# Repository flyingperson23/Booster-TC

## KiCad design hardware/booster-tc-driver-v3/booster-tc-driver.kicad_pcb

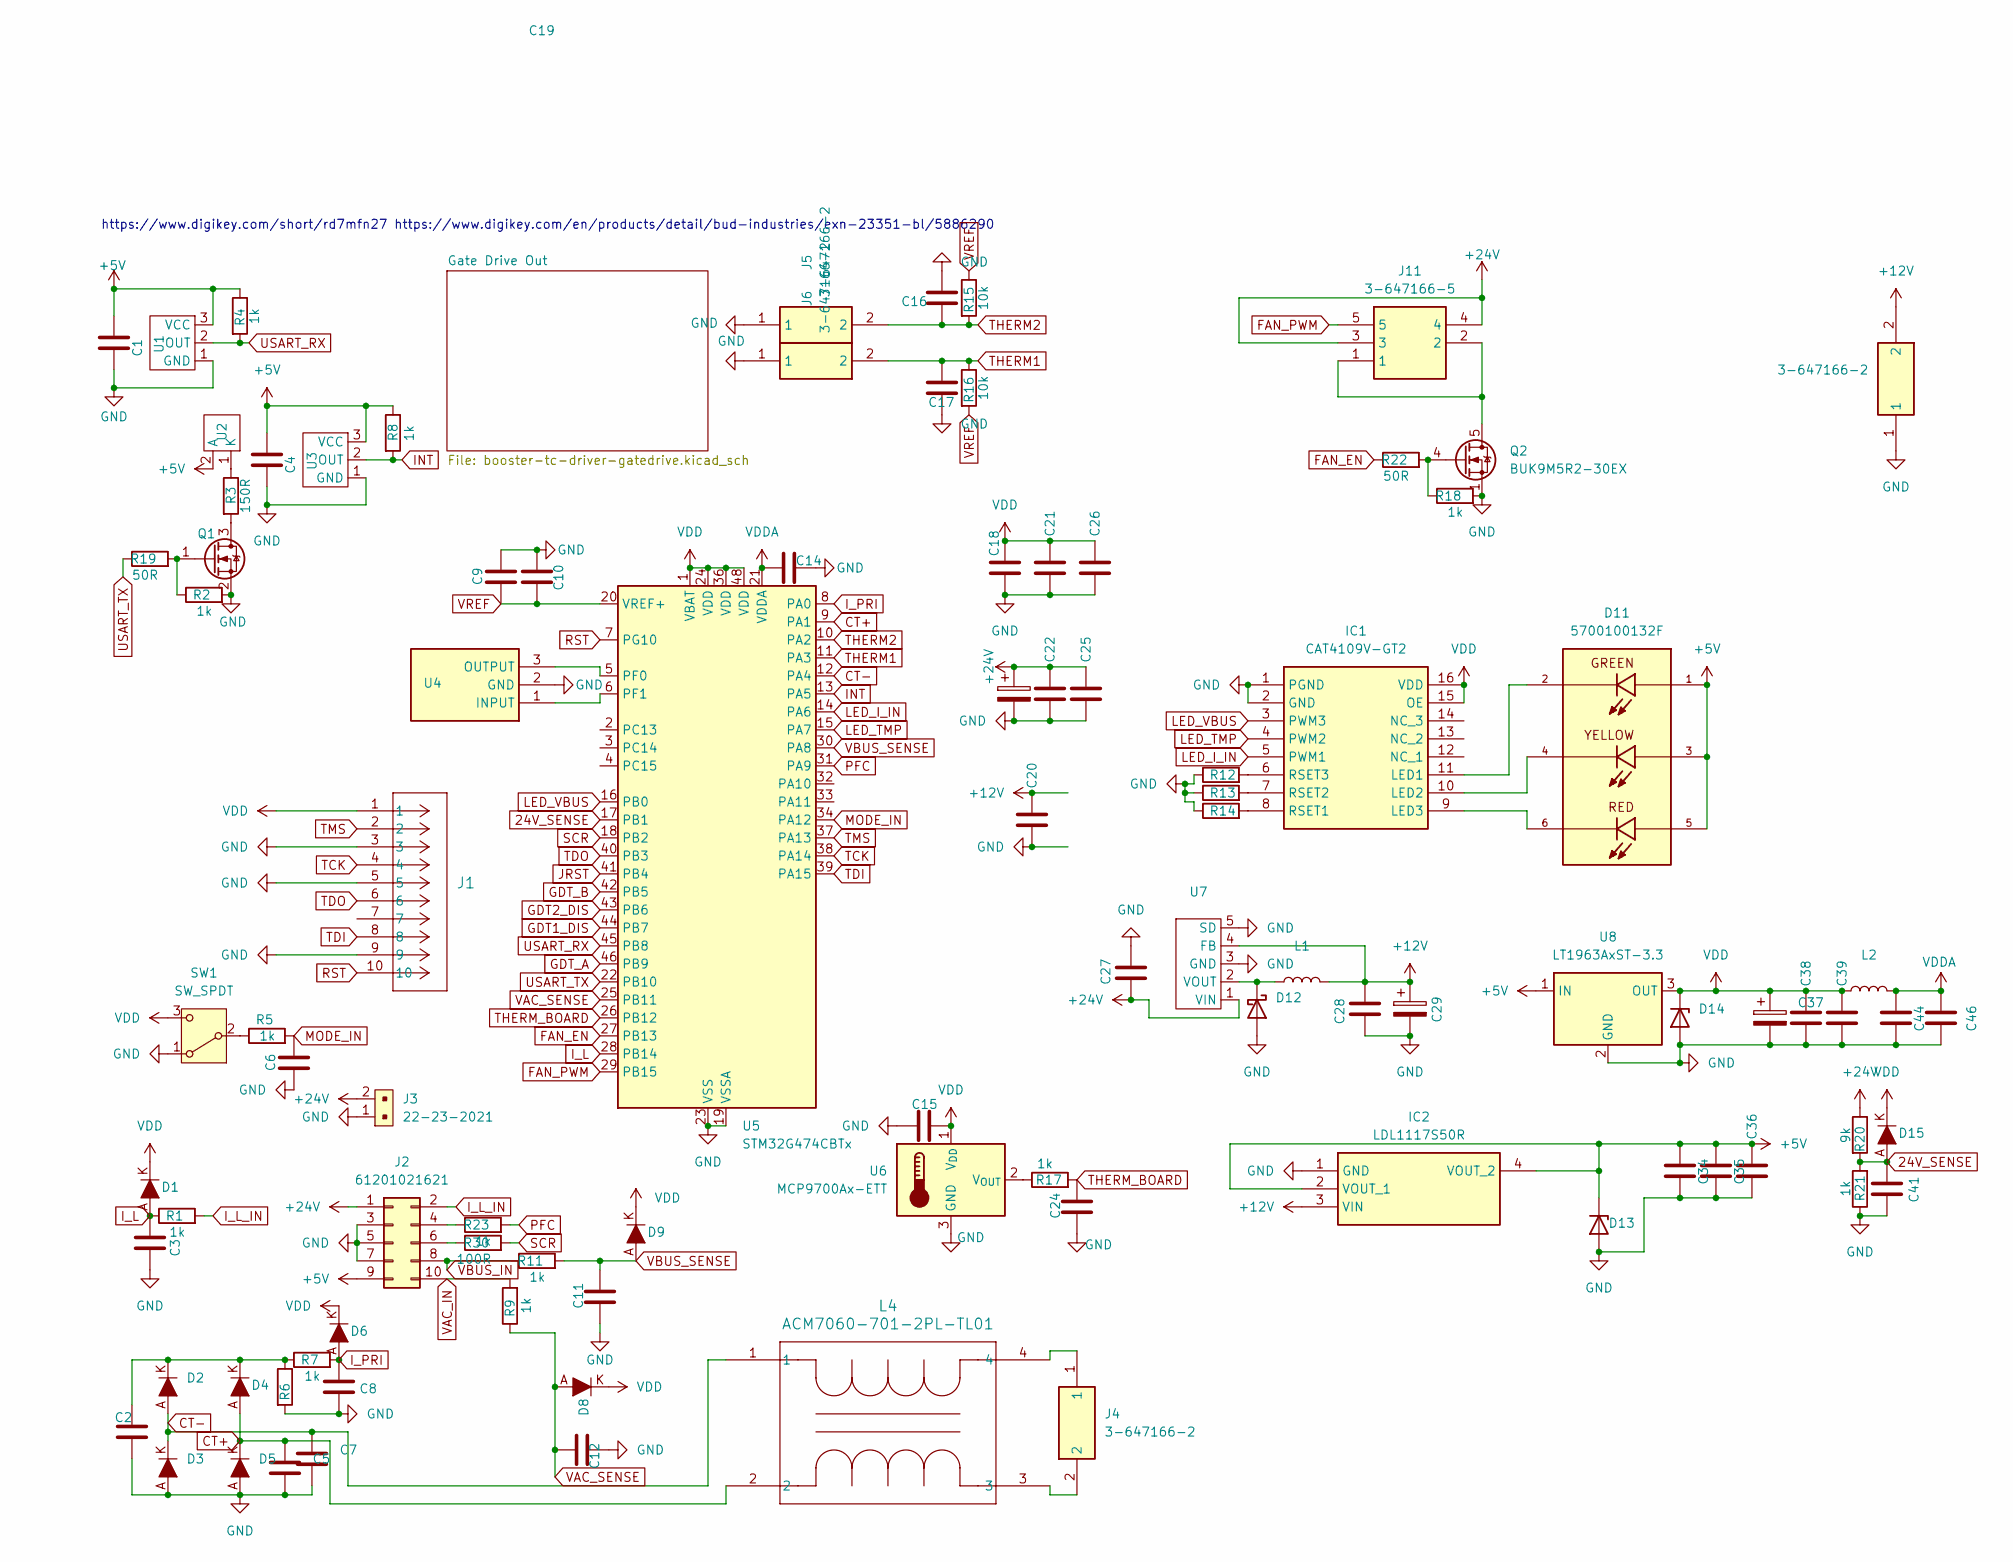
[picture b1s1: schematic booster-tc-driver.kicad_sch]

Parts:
C1, C4, C6, C9, C34, C35, C44: 2u2; C_0603_1608Metric_Pad1.08x0.95mm_HandSolder
C2, C3, C8: 1n; C_0603_1608Metric_Pad1.08x0.95mm_HandSolder
C5, C7: 150p; C_0603_1608Metric_Pad1.08x0.95mm_HandSolder
C10, C14, C15, C16, C17, C18, C20, C21, C22, C25, C26, C27, C28, C36, C38, C39, C41, C46: .1uf; C_0603_1608Metric_Pad1.08x0.95mm_HandSolder
C11, C12, C24: 10n; C_0603_1608Metric_Pad1.08x0.95mm_HandSolder
C19: 330u 860020575013; 860020575013
C29, C37: 470u 860020474014; CAPPRD350W52D800H1300
D1, D2, D3, D4, D5, D6, D8, D9, D15: 1N5819HW-7-F; SOD-123; MPN 1N5819HW-7-F
D11: 5700100132F; LED_5700100132F; PARTREV N
D12: PMEG4050EP; D_SOD-128
D13: SMBJ5.0A-TR; DO-214AA
D14: SMBJ3V3; DO-214AA
IC1: CAT4109V-GT2; Mouser Part Number 698-CAT4109V-GT2
IC2: LDL1117S50R; SOT230P700X180-4N; Mouser Part Number 511-LDL1117S50R
J1: 62201021121; CONN_62201021121_WRE
J2: 61201021621; IDC-Header_2x05_P2.54mm_Vertical
J3: 22-23-2021; PinHeader_1x2_P2.54mm_Drill1.02mm; MPN 22-23-2021
J4, J5, J6, J7: 3-647166-2; 36471662; Mouser Part Number 571-3-647166-2
J11: 3-647166-5; 36471665; Mouser Part Number 571-3-647166-5
L1: 22u IHLP3232DZER220M5A; IND_IHLP-3232DZ_VIS-M
L2: 4u7 LQM2MPN4R7NG0L; LQM2MPN4R7NG0L
L4: ACM7060-701-2PL-TL01; IND_ACM7060_TDK
Q1: T2N7002AK; SOT-23
Q2: BUK9M5R2-30EX; LFPAK33
R1, R2, R4, R5, R7, R8, R9, R11, R17, R18, R21, R23: 1k; R_0603_1608Metric_Pad0.98x0.95mm_HandSolder
R3: 150R; R_0603_1608Metric_Pad0.98x0.95mm_HandSolder
R6: 2R2 35222R2JT; R_2512_6332Metric_Pad1.40x3.35mm_HandSolder
R12, R13, R14: 24k9; R_0603_1608Metric_Pad0.98x0.95mm_HandSolder
R15, R16: 10k; R_0603_1608Metric_Pad0.98x0.95mm_HandSolder
R19, R22: 50R; R_0603_1608Metric_Pad0.98x0.95mm_HandSolder
R20: 9k; R_0603_1608Metric_Pad0.98x0.95mm_HandSolder
R30: 100R; R_0603_1608Metric_Pad0.98x0.95mm_HandSolder
SW1: SW_SPDT; B12JV
U1, U3: IF-D95T << must be T; IF-D95
U2: IF-E96E
U4: CSTNE8M00G550000R0; CSTNE16M0V530000R0; Mouser Part Number 81-CSTNE8M00G550000R
U5: STM32G474CBTx; LQFP-48_7x7mm_P0.5mm
U6: MCP9700Ax-ETT; SOT-23
U7: AP1501A-12K5G-13; TO-263-5_TabPin3
U8: LT1963AxST-3.3; SOT-223-3_TabPin2

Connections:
24V_SENSE: C41.1, D15.A, R20.2, R21.2, U5.17 (PB1)
+5V: C1.1, C4.1, C34.1, C35.1, C36.1, D11.1, D11.3, D11.5, D13.1 (K), IC2.2 (VOUT_1), IC2.4 (VOUT_2), J2.9, R4.1, R8.1, U1.3 (VCC), U2.2 (A), U3.3 (VCC), U8.1 (IN)
+12V: C20.1, C28.1, C29.1, IC2.3 (VIN), J7.2, L1.2, U7.4 (FB); also elsewhere on the board
+24V: C19.1, C22.1, C25.1, C27.2, J2.1, J3.2, J11.3, J11.4, R20.1, U7.1 (VIN); also elsewhere on the board
CT+: C5.1, D4.A, D5.K, L4.2, U5.9 (PA1)
CT-: C7.1, D2.A, D3.K, L4.1, U5.12 (PA4)
FAN_EN: R22.1, U5.27 (PB13)
FAN_PWM: J11.5, U5.29 (PB15)
GDT1_DIS: U5.44 (PB7); also elsewhere on the board
GDT2_DIS: U5.43 (PB6); also elsewhere on the board
GDT_A: U5.46 (PB9); also elsewhere on the board
GDT_B: U5.42 (PB5); also elsewhere on the board
GND: C1.2, C2.2, C3.2, C4.2, C5.2, C6.2, C7.2, C8.2, C9.1, C10.1, C11.2, C12.2, C14.2, C15.1, C16.2, C17.1, C18.2, C19.2, C20.2, C21.2, C22.2, C24.2, C25.2, C26.2, C27.1, C28.2, C29.2, C34.2, C35.2, C36.2, C37.2, C38.2, C39.2, C41.2, C44.2, C46.2, D3.A, D5.A, D12.2 (A), D13.2 (A), D14.2 (A), IC1.1 (PGND), IC1.2 (GND), IC2.1 (GND), J1.3, J1.5, J1.9, J2.3, J2.5, J2.7, J3.1, J5.1, J6.1, J7.1, Q1.2 (S), Q2.1 (S), Q2.2 (S), Q2.3 (S), R2.2, R6.2, R12.1, R13.1, R14.1, R18.2, R21.1, SW1.1 (A), U1.1 (GND), U3.1 (GND), U4.2 (GND), U5.19 (VSSA), U5.23 (VSS), U5.35 (VSS), U5.47 (VSS), U6.3 (GND), U7.3 (GND), U7.5 (SD), U8.2 (GND); also elsewhere on the board
INT: R8.2, U3.2 (OUT), U5.13 (PA5)
I_L: C3.1, D1.A, R1.1, U5.28 (PB14)
I_L_IN: J2.2, R1.2
I_PRI: C8.1, D6.A, R7.2, U5.8 (PA0)
JRST: U5.41 (PB4)
LED_I_IN: IC1.5 (PWM1), U5.14 (PA6)
LED_TMP: IC1.4 (PWM2), U5.15 (PA7)
LED_VBUS: IC1.3 (PWM3), U5.16 (PB0)
MODE_IN: C6.1, R5.2, U5.34 (PA12)
unnamed: C2.1, D2.K, D4.K, R6.1, R7.1
unnamed: D12.1 (K), L1.1, U7.2 (VOUT)
unnamed: D11.2, IC1.11 (LED1)
unnamed: D11.4, IC1.10 (LED2)
unnamed: D11.6, IC1.9 (LED3)
unnamed: IC1.8 (RSET1), R14.2
unnamed: IC1.7 (RSET2), R13.2
unnamed: IC1.6 (RSET3), R12.2
unnamed: J2.4, R23.1
unnamed: J2.6, R30.1
unnamed: J4.1, L4.4
unnamed: J4.2, L4.3
unnamed: Q1.3 (D), R3.2
unnamed: Q1.1 (G), R2.1, R19.2
unnamed: J11.1, J11.2, Q2.5 (D)
unnamed: Q2.4 (G), R18.1, R22.2
unnamed: R5.1, SW1.2 (B)
unnamed: R3.1, U2.1 (K)
unnamed: U4.1 (INPUT), U5.6 (PF1)
unnamed: U4.3 (OUTPUT), U5.5 (PF0)
unnamed: R17.1, U6.2 (V_{OUT})
PFC: R23.2, U5.31 (PA9)
RST: J1.10, U5.7 (PG10)
SCR: R30.2, U5.18 (PB2)
TCK: J1.4, U5.38 (PA14)
TDI: J1.8, U5.39 (PA15)
TDO: J1.6, U5.40 (PB3)
THERM1: C17.2, J6.2, R16.1, U5.11 (PA3)
THERM2: C16.1, J5.2, R15.2, U5.10 (PA2)
THERM_BOARD: C24.1, R17.2, U5.26 (PB12)
TMS: J1.2, U5.37 (PA13)
USART_RX: R4.2, U1.2 (OUT), U5.45 (PB8)
USART_TX: R19.1, U5.22 (PB10)
VAC_IN: J2.10, R9.2
VAC_SENSE: C12.1, D8.A, R9.1, U5.25 (PB11)
VBUS_IN: J2.8, R11.1
VBUS_SENSE: C11.1, D9.A, R11.2, U5.30 (PA8)
VDD: C15.2, C18.1, C21.1, C26.1, C37.1, C38.1, C39.1, D1.K, D6.K, D8.K, D9.K, D14.1 (K), D15.K, IC1.15 (OE), IC1.16 (VDD), J1.1, L2.1, SW1.3 (C), U5.1 (VBAT), U5.24 (VDD), U5.36 (VDD), U5.48 (VDD), U6.1 (V_{DD}), U8.3 (OUT)
VDDA: C14.1, C44.1, C46.1, L2.2, U5.21 (VDDA)
VREF: C9.2, C10.2, R15.1, R16.2, U5.20 (VREF+)

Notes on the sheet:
https://www.digikey.com/short/rd7mfn27 https://www.digikey.com/en/products/detail/bud-industries/exn-23351-bl/5886290

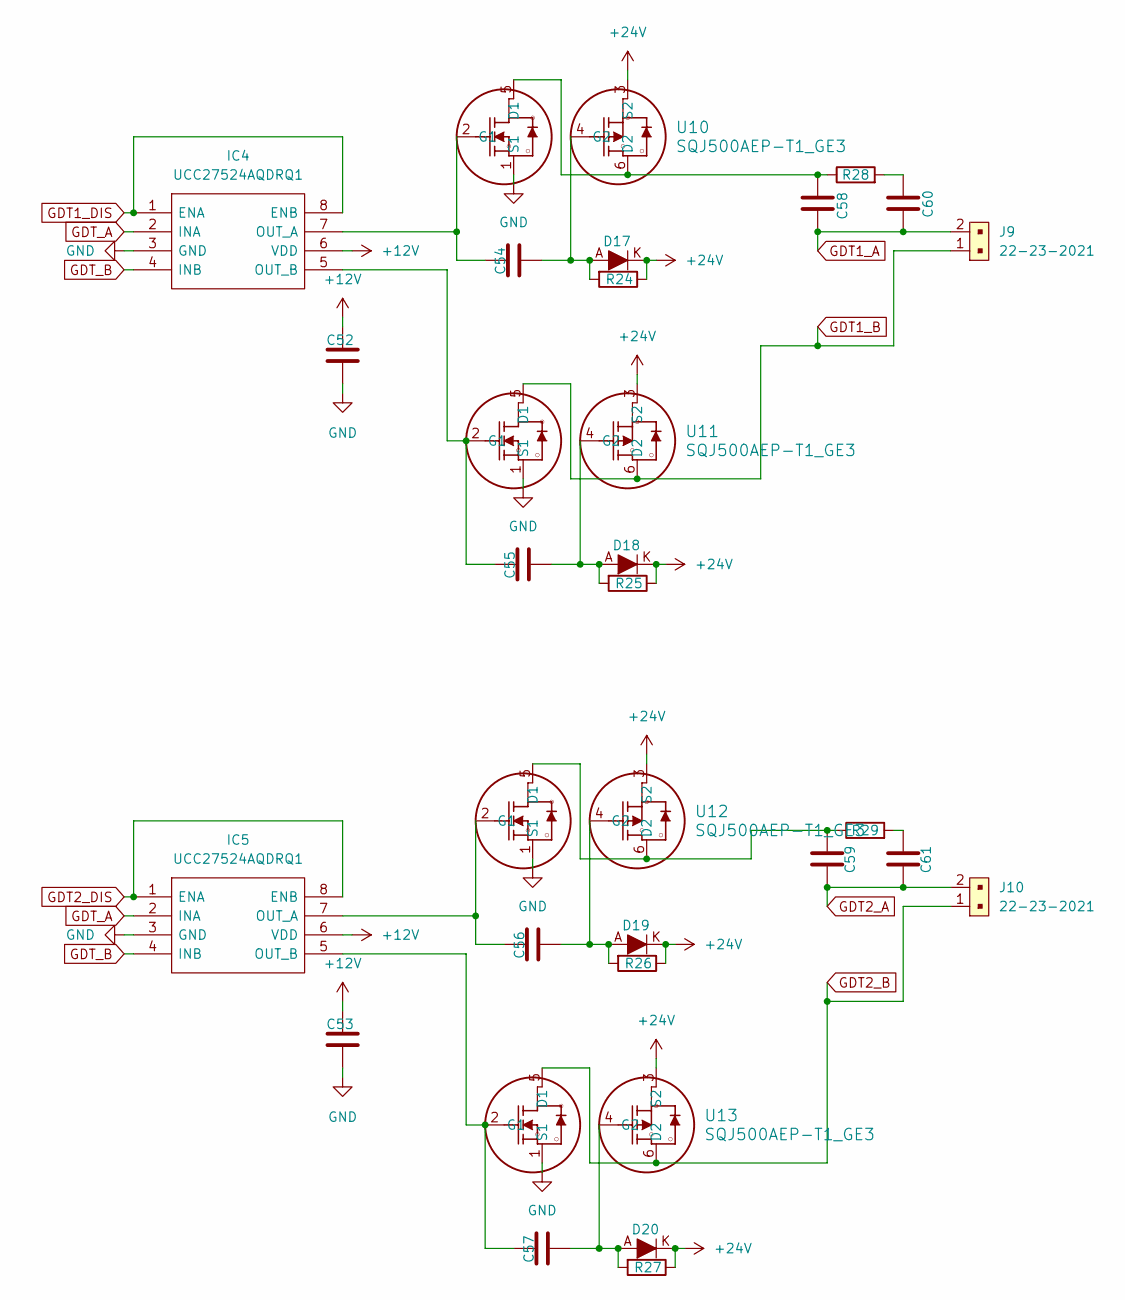
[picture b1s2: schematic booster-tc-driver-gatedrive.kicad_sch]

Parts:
C52, C53: .1uf; C_0603_1608Metric_Pad1.08x0.95mm_HandSolder
C54, C55, C56, C57: .1uf 885012208087; C_1206_3216Metric_Pad1.33x1.80mm_HandSolder
C58, C59: 2u2 C3225X7R1H225K250AB; C_1210_3225Metric_Pad1.33x2.70mm_HandSolder
C60, C61: 1u C1206C105K5RACTU; C_1206_3216Metric_Pad1.33x1.80mm_HandSolder
D17, D18, D19, D20: 1N5819HW-7-F; SOD-123; MPN 1N5819HW-7-F
IC4, IC5: UCC27524AQDRQ1; SOIC127P600X175-8N; Mouser Part Number 595-UCC27524AQDRQ1
J9, J10: 22-23-2021; PinHeader_1x2_P2.54mm_Drill1.02mm; MPN 22-23-2021
R24, R25, R26, R27: 1k; R_0603_1608Metric_Pad0.98x0.95mm_HandSolder
R28, R29: 15R CRCW121015R0JNEAHP; R_1210_3225Metric_Pad1.30x2.65mm_HandSolder
U10, U11, U12, U13: SQJ500AEP-T1_GE3; SQJ500AEP-T1_GE3_VIS

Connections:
+12V: C52.1, C53.1, IC4.6 (VDD), IC5.6 (VDD); also elsewhere on the board
+24V: D17.K, D18.K, D19.K, D20.K, R24.1, R25.1, R26.1, R27.1, U10.3 (S2), U11.3 (S2), U12.3 (S2), U13.3 (S2); also elsewhere on the board
GDT1_A: C58.2, C60.2, J9.2
GDT1_B: J9.1, U11.5 (D1), U11.6 (D2)
GDT1_DIS: IC4.1 (ENA), IC4.8 (ENB); also elsewhere on the board
GDT2_A: C59.2, C61.2, J10.2
GDT2_B: J10.1, U13.5 (D1), U13.6 (D2)
GDT2_DIS: IC5.1 (ENA), IC5.8 (ENB); also elsewhere on the board
GDT_A: IC4.2 (INA), IC5.2 (INA); also elsewhere on the board
GDT_B: IC4.4 (INB), IC5.4 (INB); also elsewhere on the board
GND: C52.2, C53.2, IC4.3 (GND), IC5.3 (GND), U10.1 (S1), U11.1 (S1), U12.1 (S1), U13.1 (S1); also elsewhere on the board
unnamed: C60.1, R28.2
unnamed: C61.1, R29.2
unnamed: C54.1, IC4.7 (OUT_A), U10.2 (G1)
unnamed: C55.1, IC4.5 (OUT_B), U11.2 (G1)
unnamed: C56.1, IC5.7 (OUT_A), U12.2 (G1)
unnamed: C57.1, IC5.5 (OUT_B), U13.2 (G1)
unnamed: C58.1, R28.1, U10.5 (D1), U10.6 (D2)
unnamed: C54.2, D17.A, R24.2, U10.4 (G2)
unnamed: C55.2, D18.A, R25.2, U11.4 (G2)
unnamed: C59.1, R29.1, U12.5 (D1), U12.6 (D2)
unnamed: C56.2, D19.A, R26.2, U12.4 (G2)
unnamed: C57.2, D20.A, R27.2, U13.4 (G2)

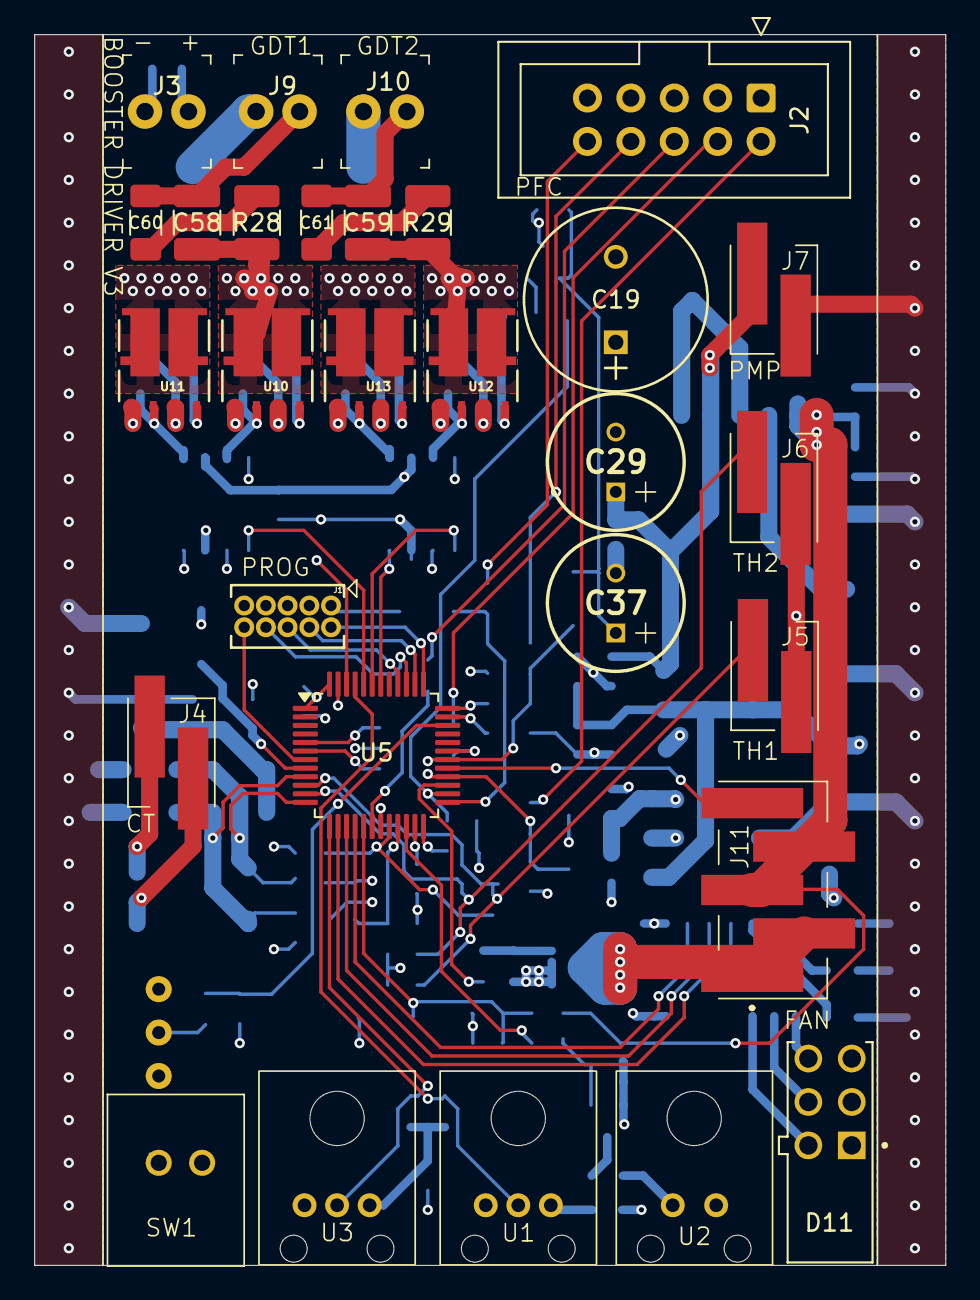
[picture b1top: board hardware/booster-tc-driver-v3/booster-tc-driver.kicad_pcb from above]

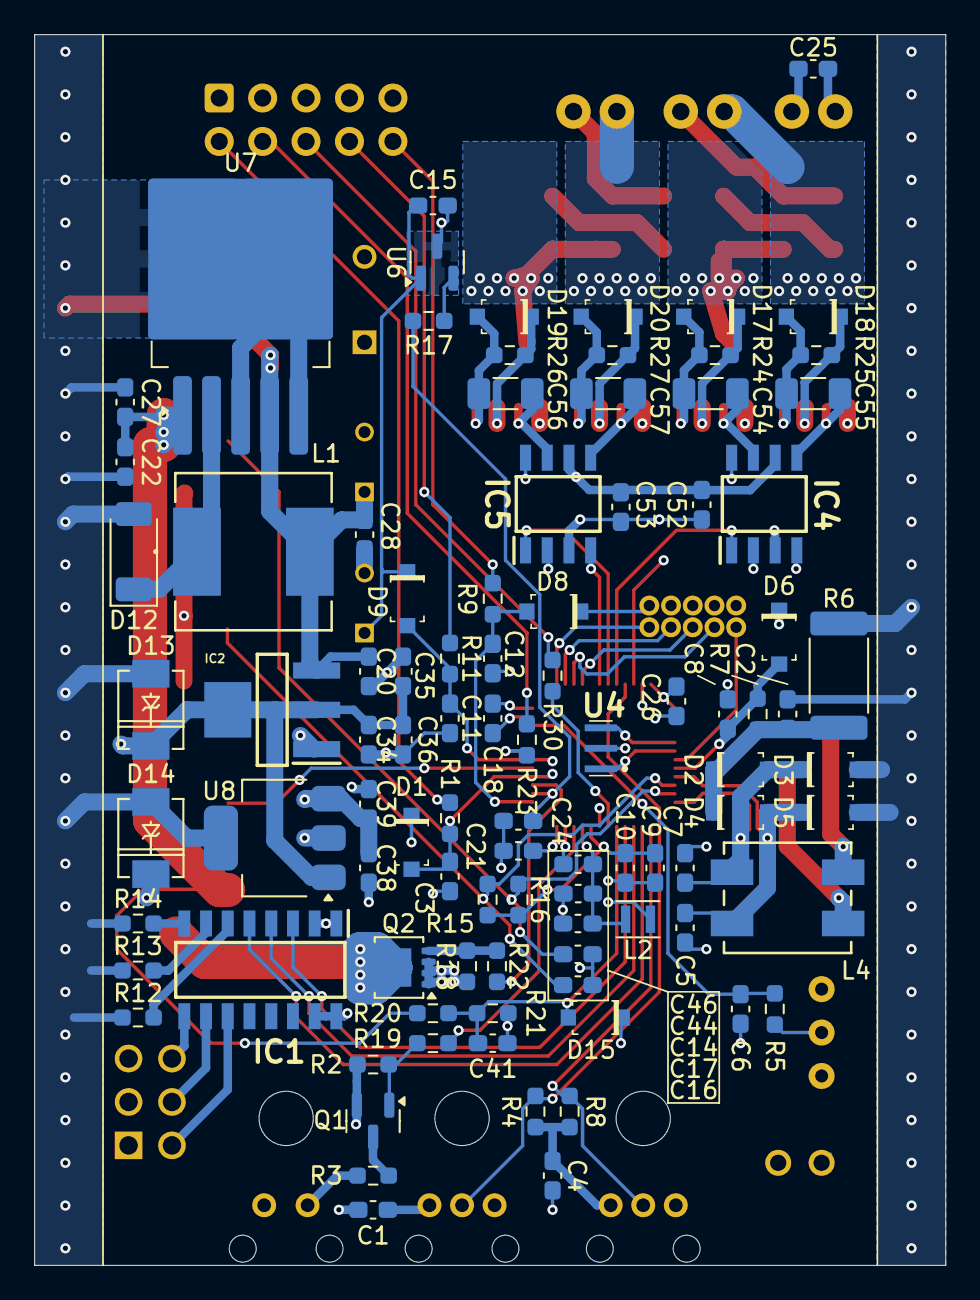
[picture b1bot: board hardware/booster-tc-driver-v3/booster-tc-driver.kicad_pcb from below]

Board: 4 copper layers, 53.3 x 72.0 mm, 124 parts (95 on the bottom side), 77 nets.

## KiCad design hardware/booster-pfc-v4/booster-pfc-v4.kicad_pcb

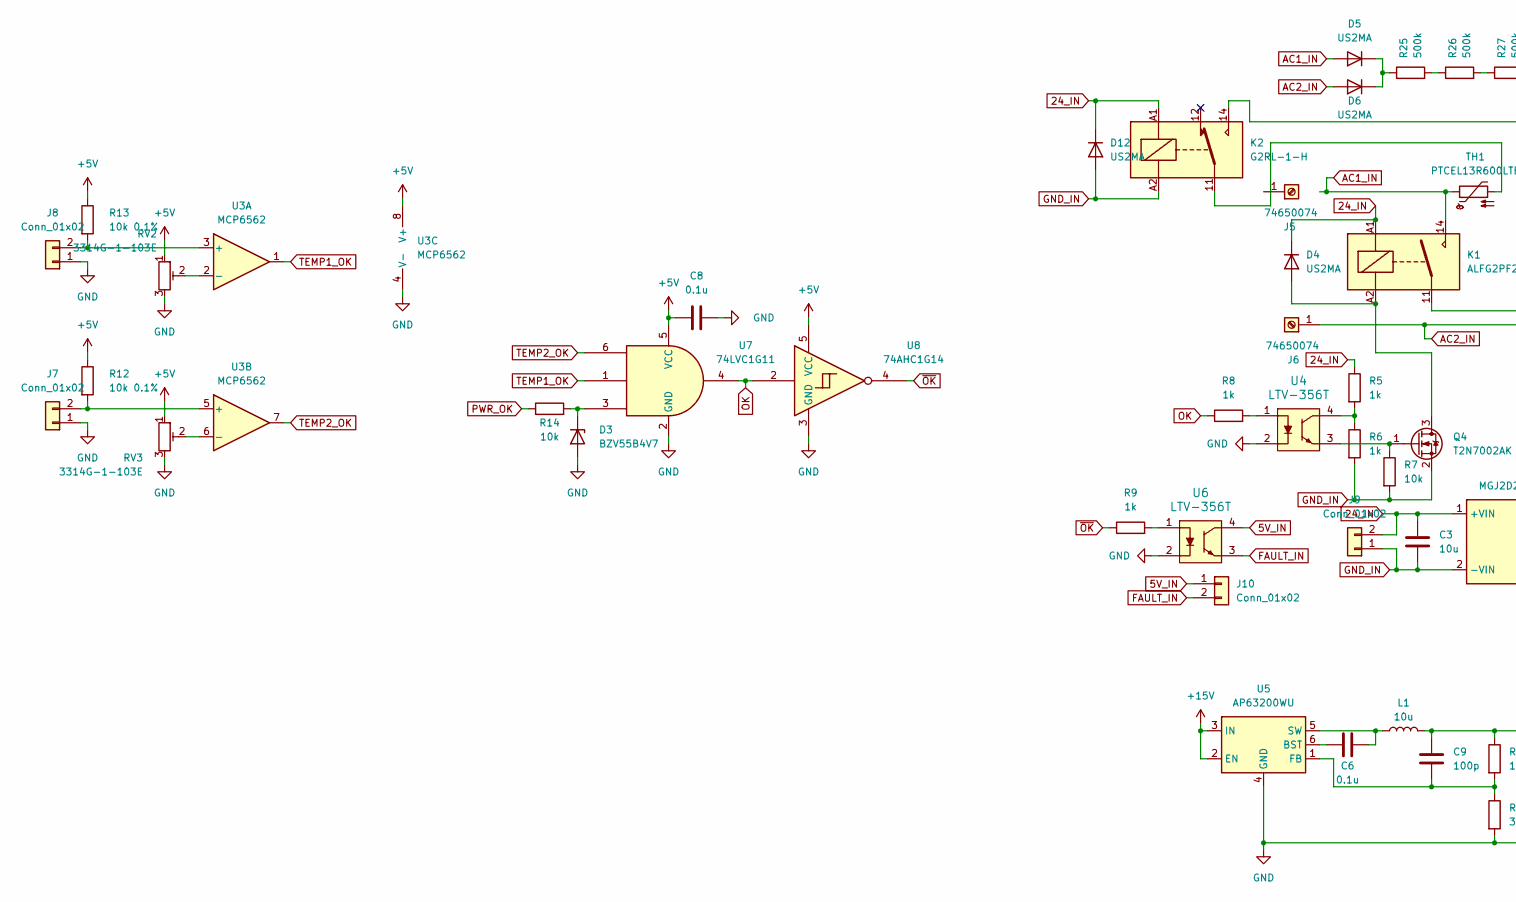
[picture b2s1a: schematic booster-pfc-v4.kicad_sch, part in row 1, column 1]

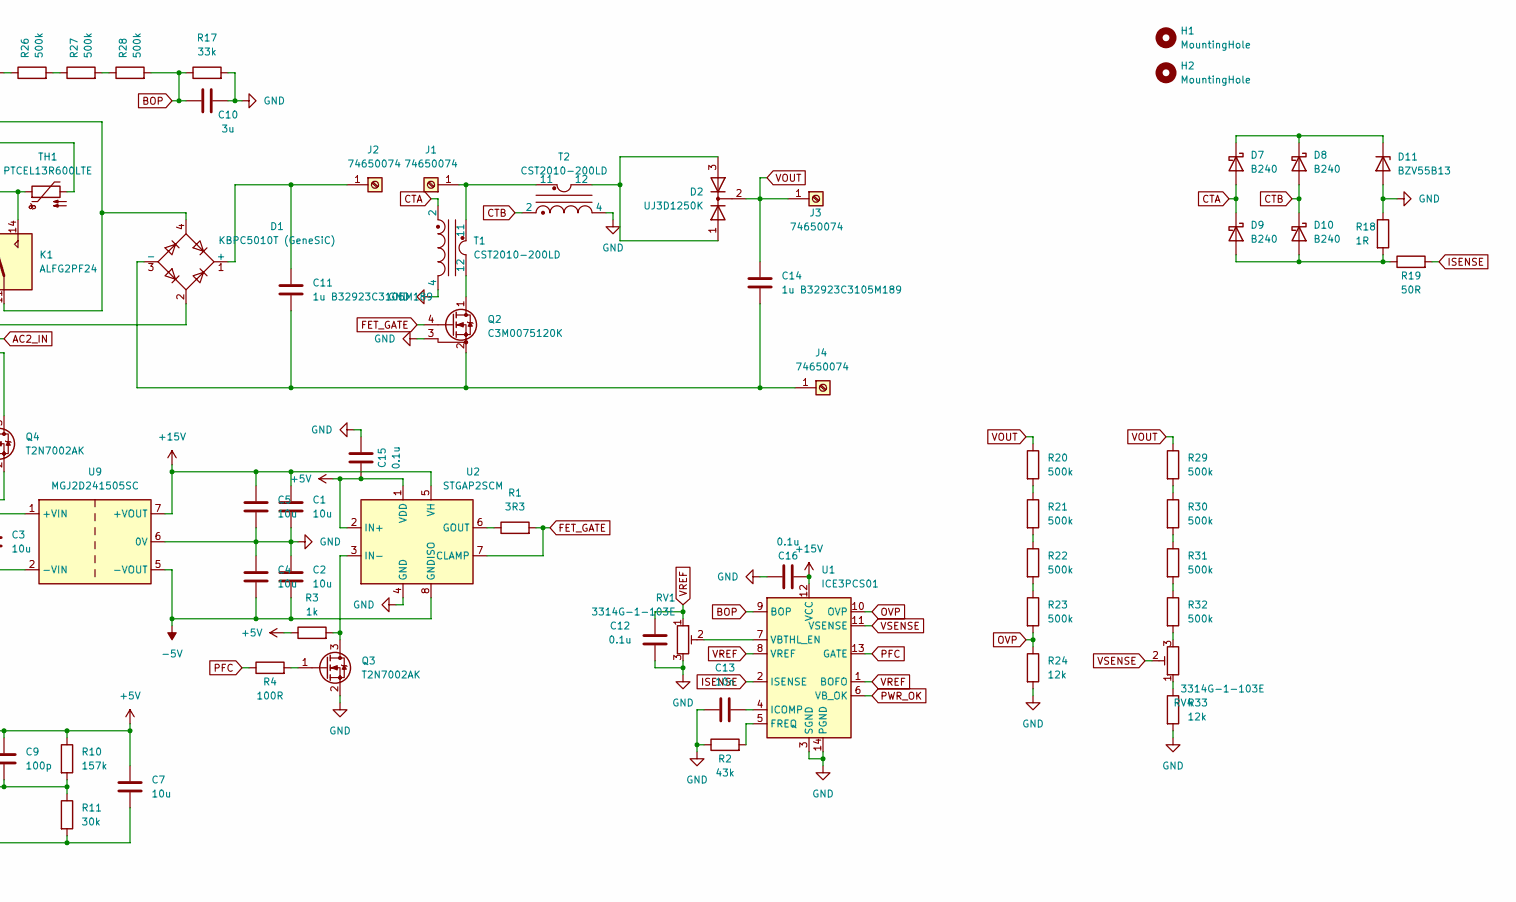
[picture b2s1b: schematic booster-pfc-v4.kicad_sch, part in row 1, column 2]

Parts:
C1, C2, C3, C4, C5, C7: 10u; C_1206_3216Metric
C6, C12, C15, C16: 0.1u; C_0805_2012Metric
C8: 0.1u; C_1206_3216Metric
C9: 100p; C_0805_2012Metric
C10: 3u; C_0805_2012Metric
C11, C14: 1u B32923C3105M189; B32923C__26.5_x_12_
C13: 10n; C_0805_2012Metric
D1: KBPC5010T (GeneSiC); DrillHole_Diode_Bridge_GeneSiC_KBPC_T
D2: UJ3D1250K; TO-247-3_Horizontal_TabDown
D3: BZV55B4V7; D_MiniMELF
D4, D5, D6, D12: US2MA; D_SMA
D7, D8, D9, D10: B240; D_SMB
D11: BZV55B13; D_MiniMELF
H1, H2: MountingHole; MountingHole_4.3mm_M4
J1, J2, J3, J4, J5, J6: 74650074; Wuerth_REDCUBE-THR_WP-THRBU_74650074_THR
J7, J8, J9, J10: Conn_01x02; Molex_KK-254_AE-6410-02A_1x02_P2.54mm_Vertical
K1: ALFG2PF24; Relay_SPST_Panasonic_ALFG_FormA_CircularHoles
K2: G2RL-1-H; Relay_SPDT_Omron_G2RL-1
L1: 10u; L_Bourns_SRP7028A_7.3x6.6mm; MPN SRP7028A-100M
Q2: C3M0075120K; TO-247-4_Horizontal_TabDown
Q3, Q4: T2N7002AK; SOT-23
R1: 3R3; R_0805_2012Metric
R2: 43k; R_0805_2012Metric
R3, R5, R6, R8, R9: 1k; R_0805_2012Metric
R4: 100R; R_0805_2012Metric
R7, R14: 10k; R_0805_2012Metric
R10: 157k; R_0805_2012Metric
R11: 30k; R_0805_2012Metric
R12, R13: 10k 0.1%; R_0805_2012Metric
R17: 33k; R_0805_2012Metric
R18: 1R; R_0805_2012Metric
R19: 50R; R_0805_2012Metric
R20, R21, R22, R23, R25, R26, R27, R28, R29, R30, R31, R32: 500k; R_0805_2012Metric
R24, R33: 12k; R_0805_2012Metric
RV1, RV2, RV3, RV4: 3314G-1-103E; Potentiometer_Bourns_3314G_Vertical
T1, T2: CST2010-200LD; Transformer_Coilcraft_CST2010
TH1: PTCEL13R600LTE; THERMISTOR_PTCEL13_5MM_VIS
U1: ICE3PCS01; SOIC-14_3.9x8.7mm_P1.27mm
U2: STGAP2SCM; SOIC-8_3.9x4.9mm_P1.27mm
U3: MCP6562; SOIC-8_3.9x4.9mm_P1.27mm
U4, U6: LTV-356T; SMD-4_4.4x3.85mm_P2.54mm; MPN LTV-356T; Digi-Key_PN 160-1337-1-ND
U5: AP63200WU; TSOT-23-6
U7: 74LVC1G11; SOT-23-6
U8: 74AHC1G14; SOT-23-5
U9: MGJ2D241505SC; Converter_DCDC_Murata_MGJ2DxxxxxxSC_THT

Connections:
5V_IN: J10.1, U6.4
24_IN: C3.1, D4.1 (K), D12.1 (K), J9.2, K1.A1, K2.A1, R5.1, U9.1 (+VIN)
+5V: C7.1, C8.1, C9.1, C15.2, L1.2, R3.1, R10.1, R12.1, R13.1, RV2.1, RV3.1, U2.1 (VDD), U2.2 (IN+), U3.8 (V+), U7.5 (VCC), U8.5 (VCC)
+15V: C1.1, C5.1, C16.2, U1.12 (VCC), U2.5 (VH), U5.2 (EN), U5.3 (IN), U9.7 (+VOUT)
-5V: C2.2, C4.2, U2.8 (GNDISO), U9.5 (-VOUT)
AC1_IN: D5.2 (A), K1.14, TH1.1
AC2_IN: D1.2, D6.2 (A), J6.1
BOP: C10.1, R17.1, R28.2, U1.9 (BOP)
CTA: D7.2 (A), D9.1 (K), T1.2
CTB: D8.2 (A), D10.1 (K), T2.2
FAULT_IN: J10.2, U6.3
FET_GATE: Q2.4 (G), R1.2, U2.7 (CLAMP)
GND: C1.2, C2.1, C4.1, C5.2, C7.2, C8.2, C10.2, C12.1, C13.1, C15.1, C16.1, D3.2 (A), D11.2 (A), J7.1, J8.1, Q2.3 (DS), Q3.2 (S), R2.1, R11.2, R17.2, R18.1, R24.2, R33.2, RV1.3, RV2.3, RV3.3, T1.4, T2.4, U1.3 (SGND), U1.14 (PGND), U2.4 (GND), U3.4 (V-), U4.2, U5.4 (GND), U6.2, U7.2 (GND), U8.3 (GND), U9.6 (0V)
GND_IN: C3.2, D12.2 (A), J9.1, K2.A2, Q4.2 (S), R6.2, R7.2, U9.2 (-VIN)
ISENSE: R19.2, U1.2 (ISENSE)
unnamed: C11.1, D1.1 (+), J2.1
unnamed: C11.2, C14.2, D1.3 (-), J4.1, Q2.2 (S)
unnamed: D1.4, K1.11, K2.14
unnamed: D2.1 (A), D2.3 (A), T2.12
unnamed: D3.1 (K), R14.2, U7.3
unnamed: D4.2 (A), K1.A2, Q4.3 (D)
unnamed: D5.1 (K), D6.1 (K), R25.1
unnamed: D9.2 (A), D10.2 (A), R18.2, R19.1
unnamed: D7.1 (K), D8.1 (K), D11.1 (K)
unnamed: J1.1, T1.11, T2.11
unnamed: J7.2, R12.2, U3.5 (+)
unnamed: J8.2, R13.2, U3.3 (+)
unnamed: K2.11, TH1.2
unnamed: Q2.1 (D), T1.12
unnamed: Q3.3 (D), R3.2, U2.3 (IN-)
unnamed: Q3.1 (G), R4.2
unnamed: Q4.1 (G), R7.1, U4.3
unnamed: R5.2, R6.1, U4.4
unnamed: R8.2, U4.1
unnamed: R9.2, U6.1
unnamed: R20.2, R21.1
unnamed: R21.2, R22.1
unnamed: R22.2, R23.1
unnamed: R25.2, R26.1
unnamed: R26.2, R27.1
unnamed: R27.2, R28.1
unnamed: R29.2, R30.1
unnamed: R30.2, R31.1
unnamed: R31.2, R32.1
unnamed: R32.2, RV4.3
unnamed: R33.1, RV4.1
unnamed: R2.2, U1.5 (FREQ)
unnamed: C13.2, U1.4 (ICOMP)
unnamed: RV1.2, U1.7 (VBTHL_EN)
unnamed: R1.1, U2.6 (GOUT)
unnamed: RV2.2, U3.2 (-)
unnamed: RV3.2, U3.6 (-)
unnamed: C6.2, U5.6 (BST)
unnamed: C9.2, R10.2, R11.1, U5.1 (FB)
unnamed: C6.1, L1.1, U5.5 (SW)
OK: R8.1, U7.4, U8.2
OVP: R23.2, R24.1, U1.10 (OVP)
PFC: R4.1, U1.13 (GATE)
PWR_OK: R14.1, U1.6 (VB_OK)
TEMP1_OK: U3.1, U7.1
TEMP2_OK: U3.7, U7.6
VOUT: C14.1, D2.2 (K), J3.1, R20.1, R29.1
VREF: C12.2, RV1.1, U1.1 (BOFO), U1.8 (VREF)
VSENSE: RV4.2, U1.11 (VSENSE)
~OK: R9.1, U8.4

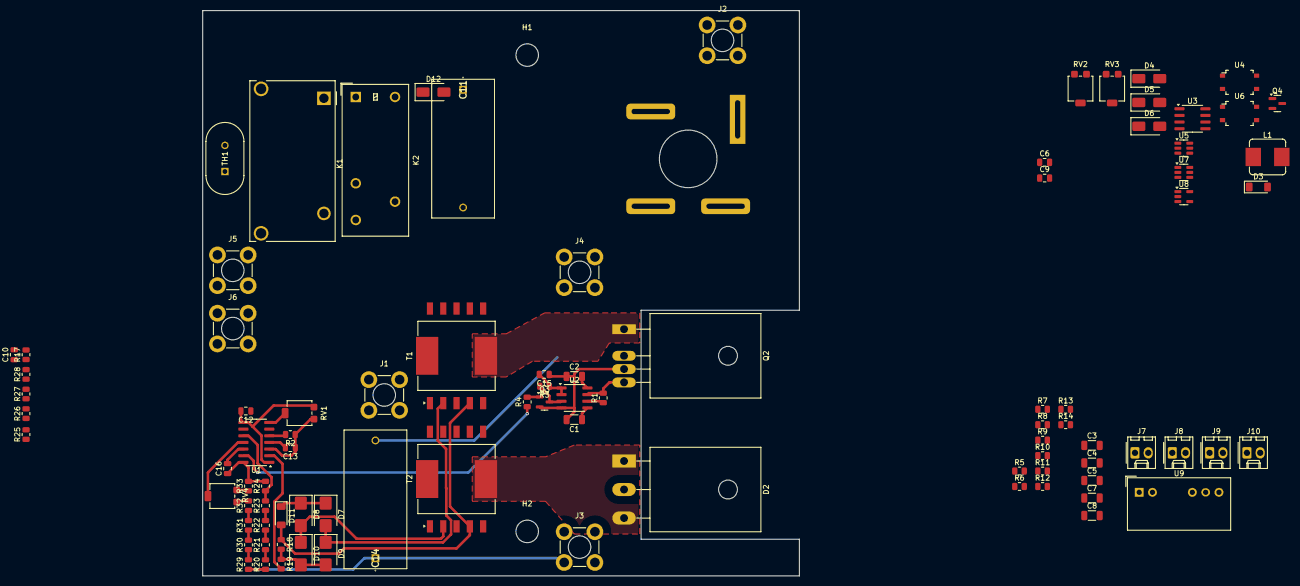
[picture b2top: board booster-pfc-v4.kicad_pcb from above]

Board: 2 copper layers, 114.0 x 108.0 mm, 93 parts (1 on the bottom side), 65 nets.

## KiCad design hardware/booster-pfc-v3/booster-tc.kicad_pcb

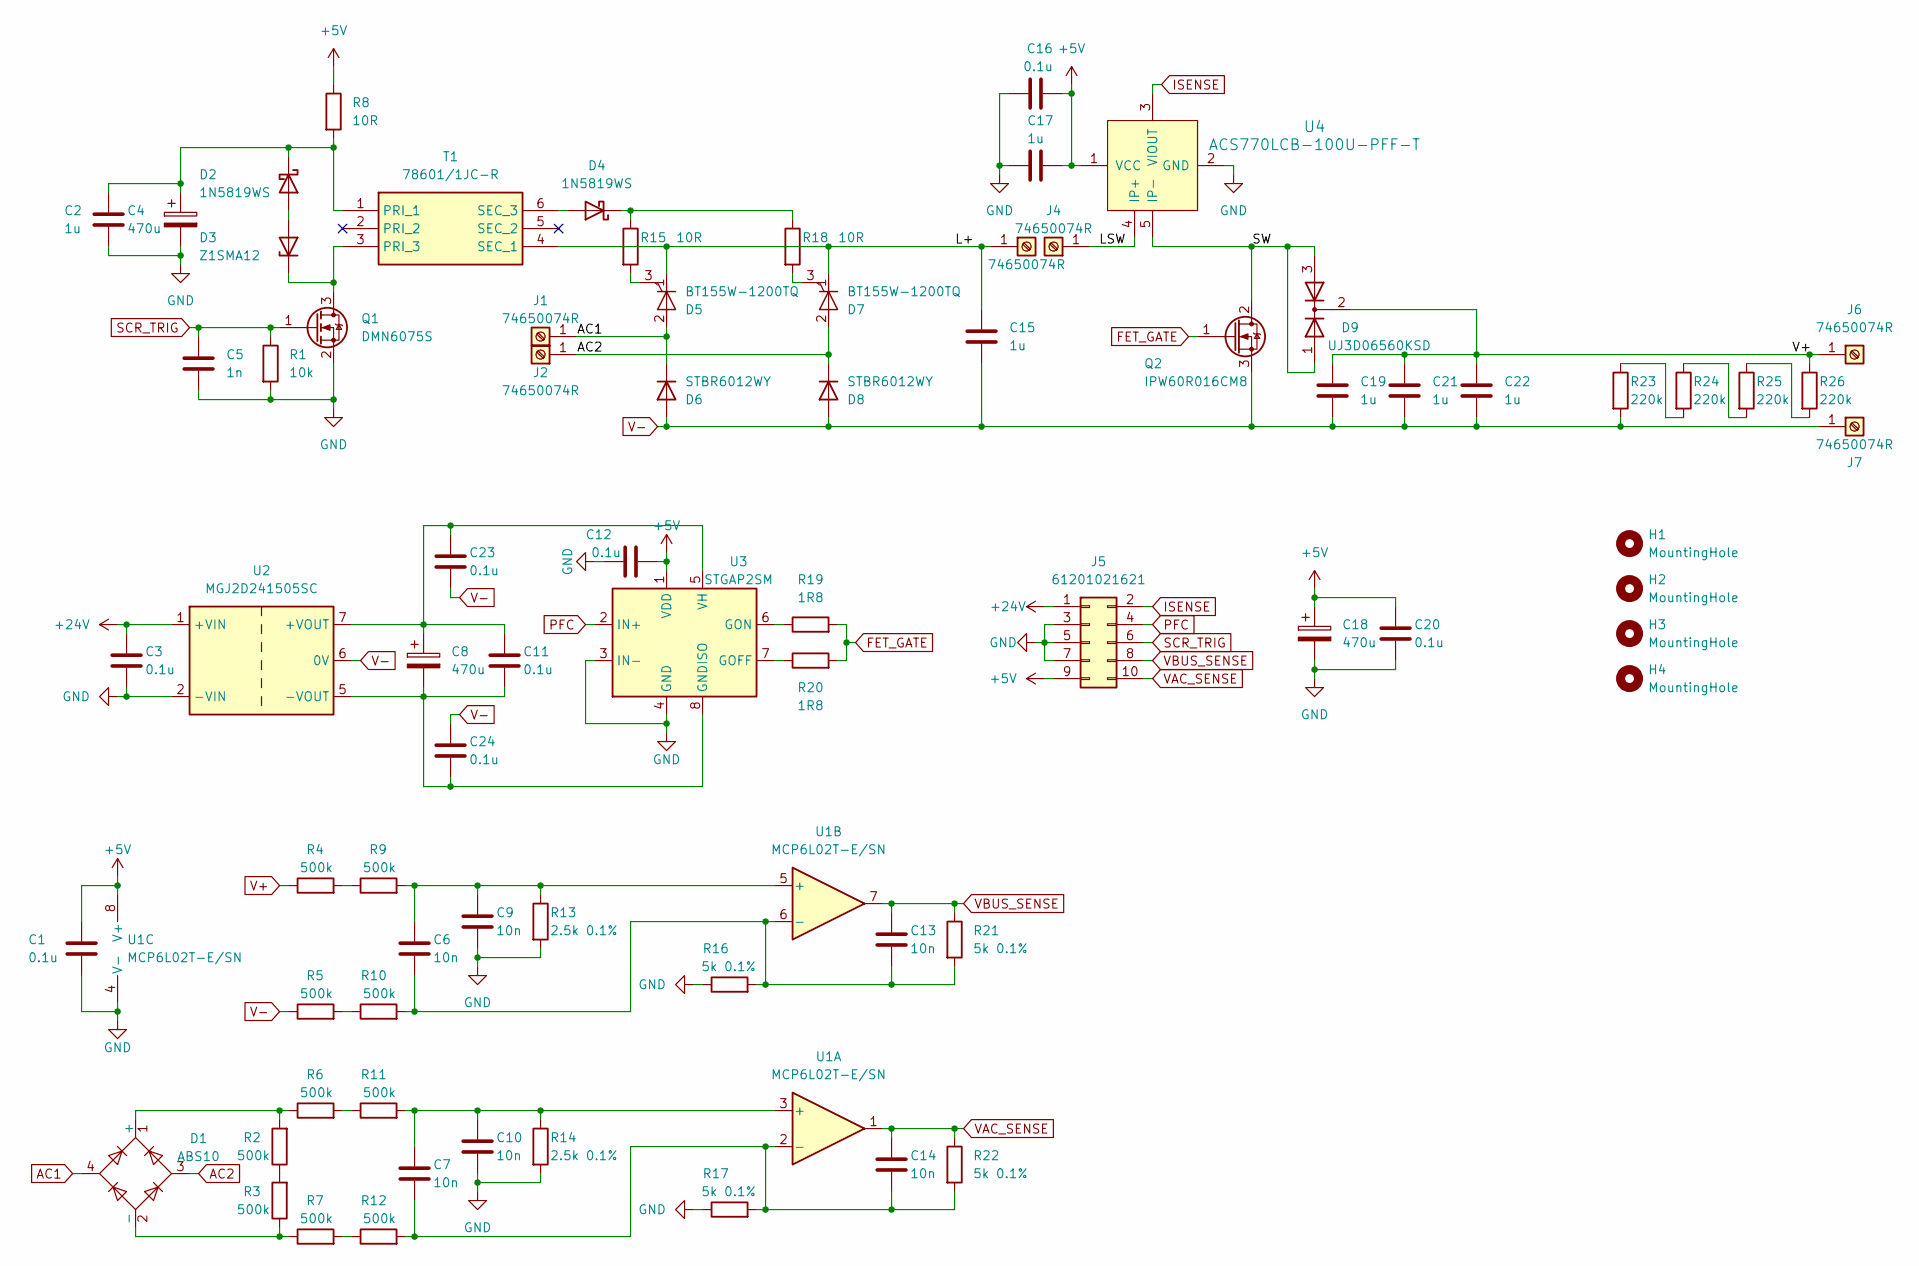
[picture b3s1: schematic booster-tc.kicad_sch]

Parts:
C1, C3, C11, C12, C16, C20, C23, C24: 0.1u; C_0805_2012Metric
C2, C17: 1u; C_0805_2012Metric
C4, C8, C18: 470u; CAPPRD350W52D800H1300; MPN 860020474014
C5: 1n; C_0805_2012Metric
C6, C7, C9, C10, C13, C14: 10n; C_0805_2012Metric
C15, C19, C21, C22: 1u; B32672P4105K000; MPN B32672P4105K000
D1: ABS10; Diode_Bridge_Diotec_ABS
D2, D4: 1N5819WS; D_SOD-323
D3: Z1SMA12; D_MicroMELF
D5, D7: BT155W-1200TQ; TO-247-3_Cutout
D6, D8: STBR6012WY; TO-247-2_Cutout
D9: UJ3D06560KSD; TO-247-3_Cutout
H1, H2, H3, H4: MountingHole; MountingHole_3.2mm_M3
J1, J2, J3, J4, J6, J7: 74650074R; Wuerth_REDCUBE-THR_WP-THRBU_74650074_THR
J5: 61201021621; IDC-Header_2x05_P2.54mm_Vertical
Q1: DMN6075S; SOT-23
Q2: IPW60R016CM8; TO-247-3_Cutout
R1: 10k; R_0805_2012Metric
R2, R3, R4, R5, R6, R7, R9, R10, R11, R12: 500k; R_0805_2012Metric
R8, R15, R18: 10R; R_0805_2012Metric
R13, R14: 2.5k 0.1%; R_0805_2012Metric
R16, R17, R21, R22: 5k 0.1%; R_0805_2012Metric
R19, R20: 1R8; R_0805_2012Metric
R23, R24, R25, R26: 220k; R_0805_2012Metric
T1: 78601/1JC-R; SOP254P1270X665-6N; Mouser Part Number 580-786019C
U1: MCP6L02T-E/SN; SOIC-8_3.9x4.9mm_P1.27mm
U2: MGJ2D241505SC; Converter_DCDC_Murata_MGJ2DxxxxxxSC_THT
U3: STGAP2SM; SOIC-8_3.9x4.9mm_P1.27mm
U4: ACS770LCB-100U-PFF-T; CB-5_Formed_Leads; MPN ACS770LCB-100U-PFF-T; Digi-Key_PN 620-1543-5-ND

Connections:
+5V: C1.1, C12.2, C16.2, C17.1, C18.1, C20.1, J5.9, R8.1, U1.8 (V+), U3.1 (VDD), U4.1 (VCC)
+24V: C3.1, J5.1, U2.1 (+VIN)
/L+: C15.1, D5.1 (K), D7.1 (K), J3.1, T1.4 (SEC_1)
/LSW: J4.1, U4.4 (IP+)
/SW: D9.1 (A), D9.3 (A), Q2.2 (D), U4.5 (IP-)
AC1: D1.4, D5.2 (A), D6.1 (K), J1.1
AC2: D1.3, D7.2 (A), D8.1 (K), J2.1
FET_GATE: Q2.1 (G), R19.2, R20.2
GND: C1.2, C2.2, C3.2, C4.2, C5.2, C9.2, C10.2, C12.1, C16.1, C17.2, C18.2, C20.2, J5.3, J5.5, J5.7, Q1.2 (S), R1.2, R13.2, R14.2, R16.1, R17.1, U1.4 (V-), U2.2 (-VIN), U3.3 (IN-), U3.4 (GND), U4.2 (GND)
ISENSE: J5.2, U4.3 (VIOUT)
unnamed: D1.1 (+), R2.2, R6.1
unnamed: D1.2 (-), R3.1, R7.1
unnamed: D2.2 (A), D3.2 (A)
unnamed: C2.1, C4.1, D2.1 (K), R8.2, T1.1 (PRI_1)
unnamed: D3.1 (K), Q1.3 (D), T1.3 (PRI_3)
unnamed: D4.2 (A), T1.6 (SEC_3)
unnamed: D4.1 (K), R15.1, R18.1
unnamed: D5.3 (G), R15.2
unnamed: D7.3 (G), R18.2
unnamed: R2.1, R3.2
unnamed: R4.2, R9.1
unnamed: R5.2, R10.1
unnamed: R6.2, R11.1
unnamed: R7.2, R12.1
unnamed: R23.1, R24.2
unnamed: R24.1, R25.2
unnamed: R25.1, R26.2
unnamed: C7.1, C10.1, R11.2, R14.1, U1.3 (+)
unnamed: C7.2, C14.2, R12.2, R17.2, R22.2, U1.2 (-)
unnamed: C6.1, C9.1, R9.2, R13.1, U1.5 (+)
unnamed: C6.2, C13.2, R10.2, R16.2, R21.2, U1.6 (-)
unnamed: C8.1, C11.1, C23.1, U2.7 (+VOUT), U3.5 (VH)
unnamed: C8.2, C11.2, C24.2, U2.5 (-VOUT), U3.8 (GNDISO)
unnamed: R20.1, U3.7 (GOFF)
unnamed: R19.1, U3.6 (GON)
PFC: J5.4, U3.2 (IN+)
SCR_TRIG: C5.1, J5.6, Q1.1 (G), R1.1
V+: C19.1, C21.1, C22.1, D9.2 (K), J6.1, R4.1, R26.1
V-: C15.2, C19.2, C21.2, C22.2, C23.2, C24.1, D6.2 (A), D8.2 (A), J7.1, Q2.3 (S), R5.1, R23.2, U2.6 (0V)
VAC_SENSE: C14.1, J5.10, R22.1, U1.1
VBUS_SENSE: C13.1, J5.8, R21.1, U1.7
